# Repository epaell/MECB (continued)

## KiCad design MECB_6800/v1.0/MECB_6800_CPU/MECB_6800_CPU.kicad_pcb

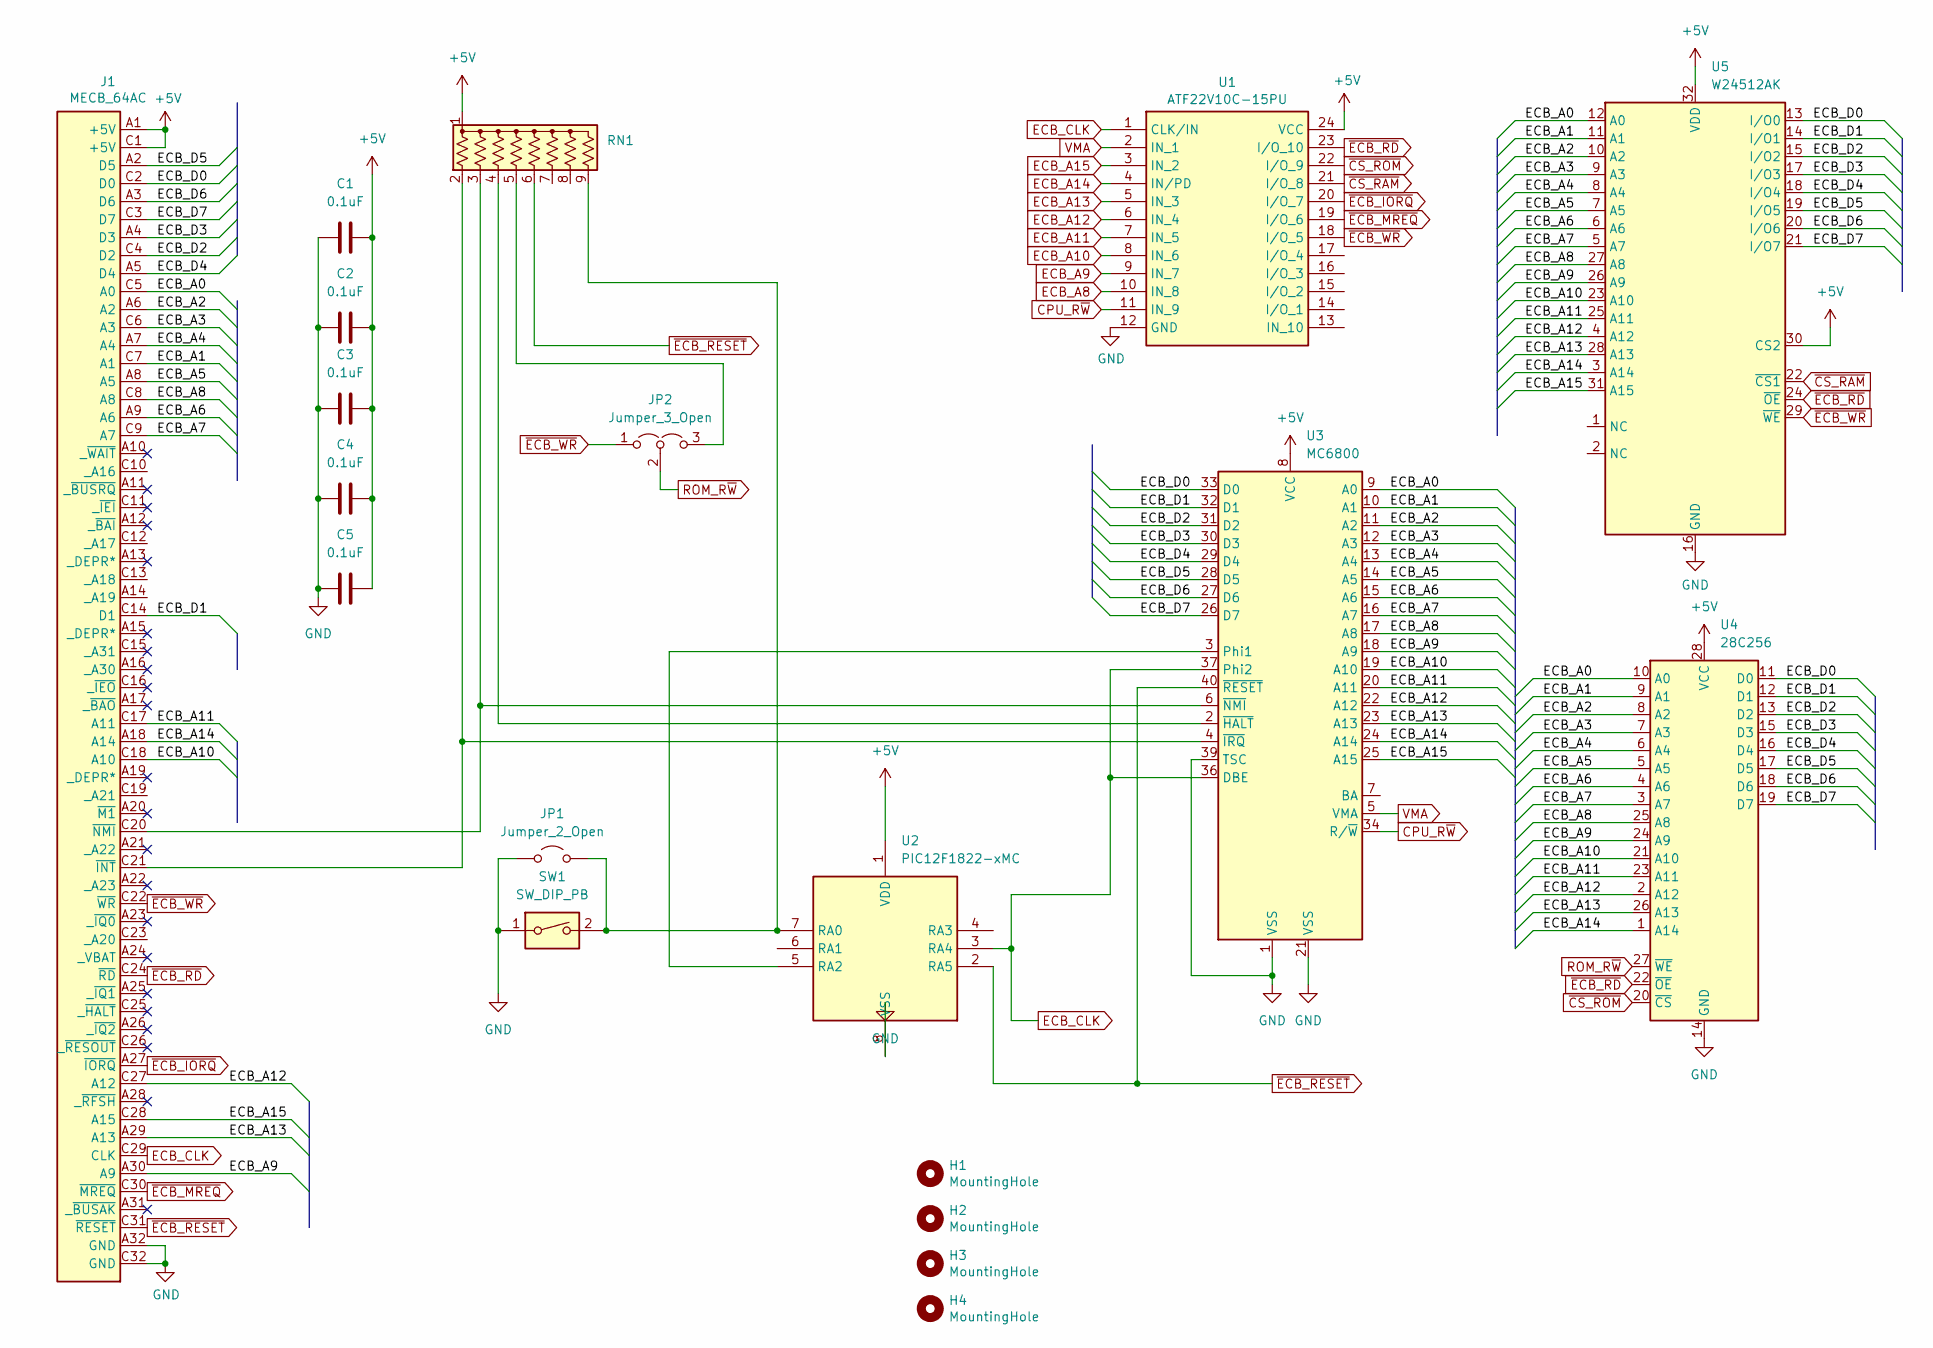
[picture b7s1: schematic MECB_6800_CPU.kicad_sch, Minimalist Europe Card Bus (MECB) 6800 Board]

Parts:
C1, C2, C3, C4, C5: 0.1uF; C_Disc_D5.0mm_W2.5mm_P5.00mm
H1, H2, H3, H4: MountingHole; MountingHole_3.2mm_M3
J1: MECB_64AC; DIN41612_C_2x32_C64AC_Male_Horizontal_THT
JP1: Jumper_2_Open; PinHeader_1x02_P2.54mm_Vertical
JP2: Jumper_3_Open; PinHeader_1x03_P2.54mm_Vertical
RN1: R_Network08_US; R_Array_SIP9
SW1: SW_DIP_PB; SW_Tactile_Straight_KSA0Axx1LFTR
U1: ATF22V10C-15PU; DIP-24_W7.62mm_Socket_LongPads; Mouser Part Number 556-AF22V10C15PU
U2: PIC12F1822-xMC; DIP-8_W7.62mm_Socket_LongPads
U3: MC6800; DIP-40_W15.24mm_Socket_LongPads
U4: 28C256; DIP-28_W15.24mm_Socket_LongPads
U5: W24512AK; DIP-32_W7.62mm

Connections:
+5V: C1.2, C2.2, C3.2, C4.2, C5.2, J1.A1 (+5V), J1.C1 (+5V), RN1.1 (common), U1.24 (VCC), U2.1 (VDD), U3.8 (VCC), U4.28 (VCC), U5.30 (CS2), U5.32 (VDD)
/ECB_A0: J1.C5 (A0), U3.9 (A0), U4.10 (A0), U5.12 (A0)
/ECB_A1: J1.C7 (A1), U3.10 (A1), U4.9 (A1), U5.11 (A1)
/ECB_A2: J1.A6 (A2), U3.11 (A2), U4.8 (A2), U5.10 (A2)
/ECB_A3: J1.C6 (A3), U3.12 (A3), U4.7 (A3), U5.9 (A3)
/ECB_A4: J1.A7 (A4), U3.13 (A4), U4.6 (A4), U5.8 (A4)
/ECB_A5: J1.A8 (A5), U3.14 (A5), U4.5 (A5), U5.7 (A5)
/ECB_A6: J1.A9 (A6), U3.15 (A6), U4.4 (A6), U5.6 (A6)
/ECB_A7: J1.C9 (A7), U3.16 (A7), U4.3 (A7), U5.5 (A7)
/ECB_D0: J1.C2 (D0), U3.33 (D0), U4.11 (D0), U5.13 (I/O0)
/ECB_D1: J1.C14 (D1), U3.32 (D1), U4.12 (D1), U5.14 (I/O1)
/ECB_D2: J1.C4 (D2), U3.31 (D2), U4.13 (D2), U5.15 (I/O2)
/ECB_D3: J1.A4 (D3), U3.30 (D3), U4.15 (D3), U5.17 (I/O3)
/ECB_D4: J1.A5 (D4), U3.29 (D4), U4.16 (D4), U5.18 (I/O4)
/ECB_D5: J1.A2 (D5), U3.28 (D5), U4.17 (D5), U5.19 (I/O5)
/ECB_D6: J1.A3 (D6), U3.27 (D6), U4.18 (D6), U5.20 (I/O6)
/ECB_D7: J1.C3 (D7), U3.26 (D7), U4.19 (D7), U5.21 (I/O7)
CPU_R~W: U1.11 (IN_9), U3.34 (R/~W)
ECB_A8: J1.C8 (A8), U1.10 (IN_8), U3.17 (A8), U4.25 (A8), U5.27 (A8)
ECB_A9: J1.A30 (A9), U1.9 (IN_7), U3.18 (A9), U4.24 (A9), U5.26 (A9)
ECB_A10: J1.C18 (A10), U1.8 (IN_6), U3.19 (A10), U4.21 (A10), U5.23 (A10)
ECB_A11: J1.C17 (A11), U1.7 (IN_5), U3.20 (A11), U4.23 (A11), U5.25 (A11)
ECB_A12: J1.C27 (A12), U1.6 (IN_4), U3.22 (A12), U4.2 (A12), U5.4 (A12)
ECB_A13: J1.A29 (A13), U1.5 (IN_3), U3.23 (A13), U4.26 (A13), U5.28 (A13)
ECB_A14: J1.A18 (A14), U1.4 (IN/PD), U3.24 (A14), U4.1 (A14), U5.3 (A14)
ECB_A15: J1.C28 (A15), U1.3 (IN_2), U3.25 (A15), U5.31 (A15)
ECB_CLK: J1.C29 (CLK), U1.1 (CLK/IN), U2.3 (RA4), U3.36 (DBE), U3.37 (Phi2)
GND: C1.1, C2.1, C3.1, C4.1, C5.1, J1.A32 (GND), J1.C32 (GND), JP1.1 (A), SW1.1, U1.12 (GND), U2.8 (VSS), U3.1 (VSS), U3.21 (VSS), U3.39 (TSC), U4.14 (GND), U5.16 (GND)
unnamed: J1.C21 (~INT), RN1.2 (R1), U3.4 (~IRQ)
unnamed: J1.C20 (~NMI), RN1.3 (R2), U3.6 (~NMI)
unnamed: JP1.2 (B), RN1.9 (R8), SW1.2, U2.7 (RA0)
unnamed: JP2.3 (B), RN1.5 (R4)
unnamed: RN1.4 (R3), U3.2 (~HALT)
unnamed: U2.5 (RA2), U3.3 (Phi1)
ROM_R~W: JP2.2 (C), U4.27 (~WE)
VMA: U1.2 (IN_1), U3.5 (VMA)
~CS_RAM: U1.21 (I/O_8), U5.22 (~CS1)
~CS_ROM: U1.22 (I/O_9), U4.20 (~CS)
~ECB_IORQ: J1.A27 (~IORQ), U1.20 (I/O_7)
~ECB_MREQ: J1.C30 (~MREQ), U1.19 (I/O_6)
~ECB_RD: J1.C24 (~RD), U1.23 (I/O_10), U4.22 (~OE), U5.24 (~OE)
~ECB_RESET: J1.C31 (~RESET), RN1.6 (R5), U2.2 (RA5), U3.40 (~RESET)
~ECB_WR: J1.C22 (~WR), JP2.1 (A), U1.18 (I/O_5), U5.29 (~WE)

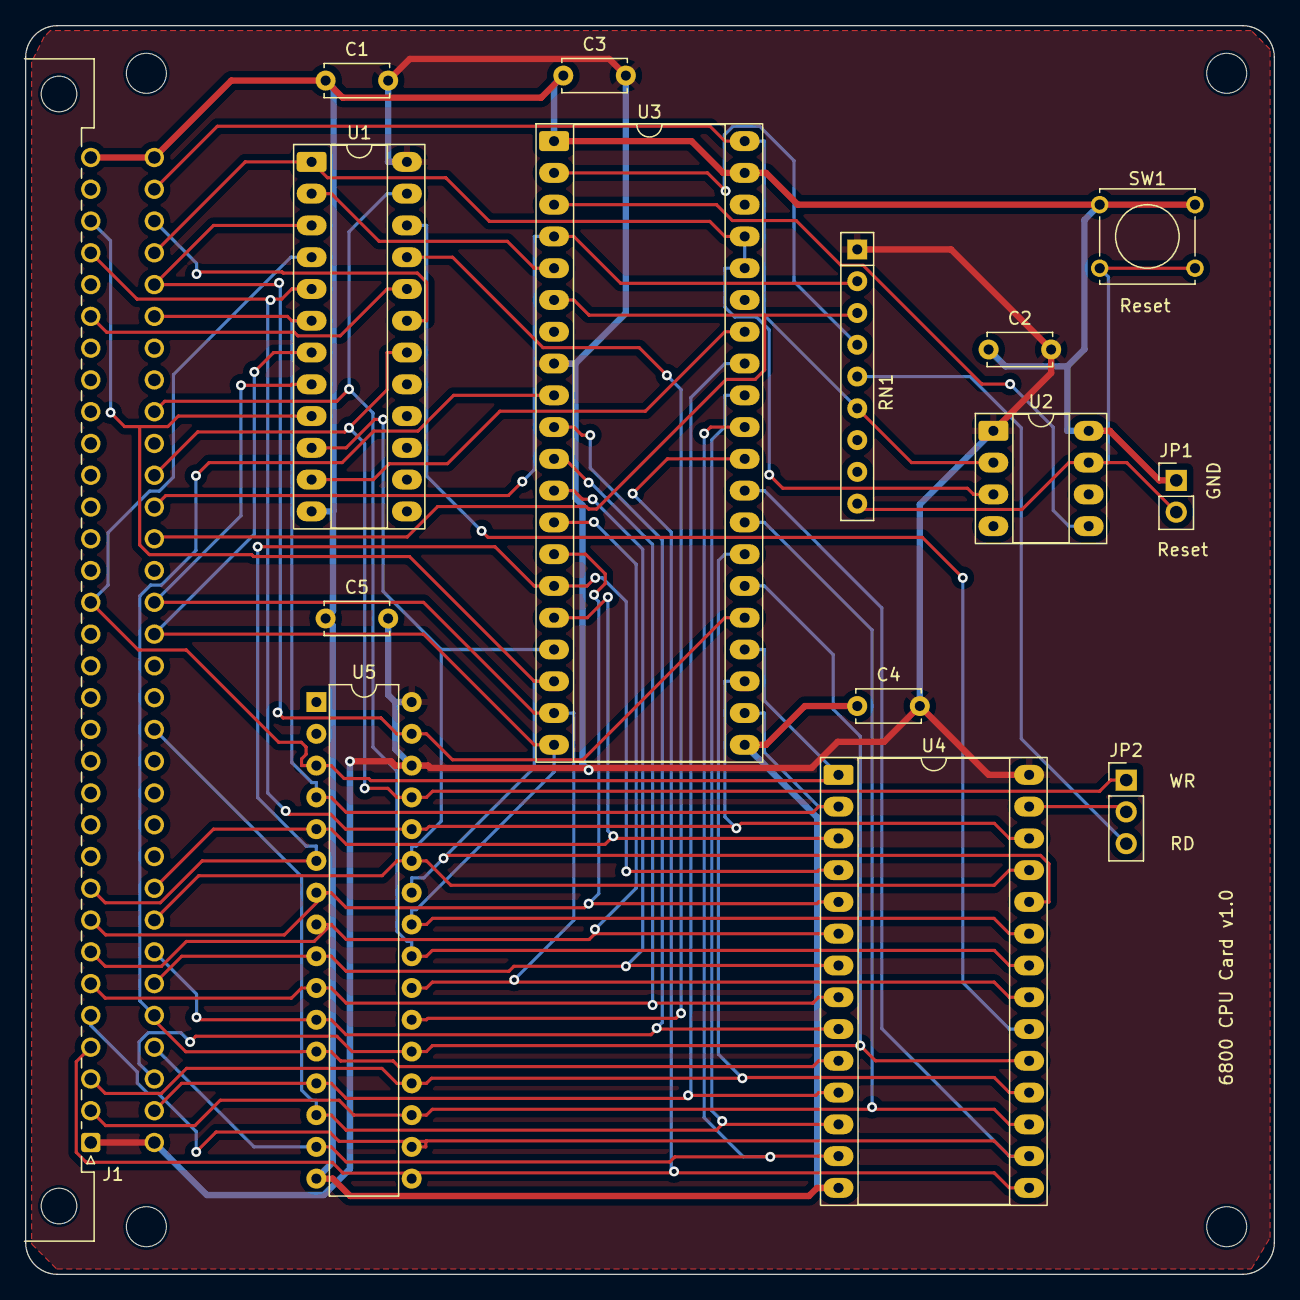
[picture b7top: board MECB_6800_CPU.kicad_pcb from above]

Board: 2 copper layers, 99.8 x 99.8 mm, 19 parts (0 on the bottom side), 43 nets.

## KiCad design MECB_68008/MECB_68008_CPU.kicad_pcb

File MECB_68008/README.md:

# MECB_68008
Development of a MECB 68008 system. Currently this board is under test so use schematics with caution (PCB layout has not been updated with fixes yet). ROM, RAM and IO access have been tested.

TODO:
- test ability to load software via Tutor - OK!
- test board with 9958 VDP card - OK!
- test interrupt functionality - Seems to work with timer.
- test ability to write to FLASH ROM and check write-protect - seems OK.
- test expansion capability - Seems to function OK with ROM expansion card.
- rework the PLD to concentrate addressing in one PLD and remaining GLUE in the other. Currently it is quite messy.
- rework the PCB layout to be incorporate the bodge fixes needed for v0.1.

The GAL directory contains the definition files for the GALs used on the board.

The Tutor directory contains the monitor and enhanced BASIC (modified slightly for use with this system).

The test directory contains a number of very basic test programs to check the ROM, RAM and IO.

The SW directory contains useful 68008-related assembly routines (work in progress). Some of these may ultimately be shifted into ROM.

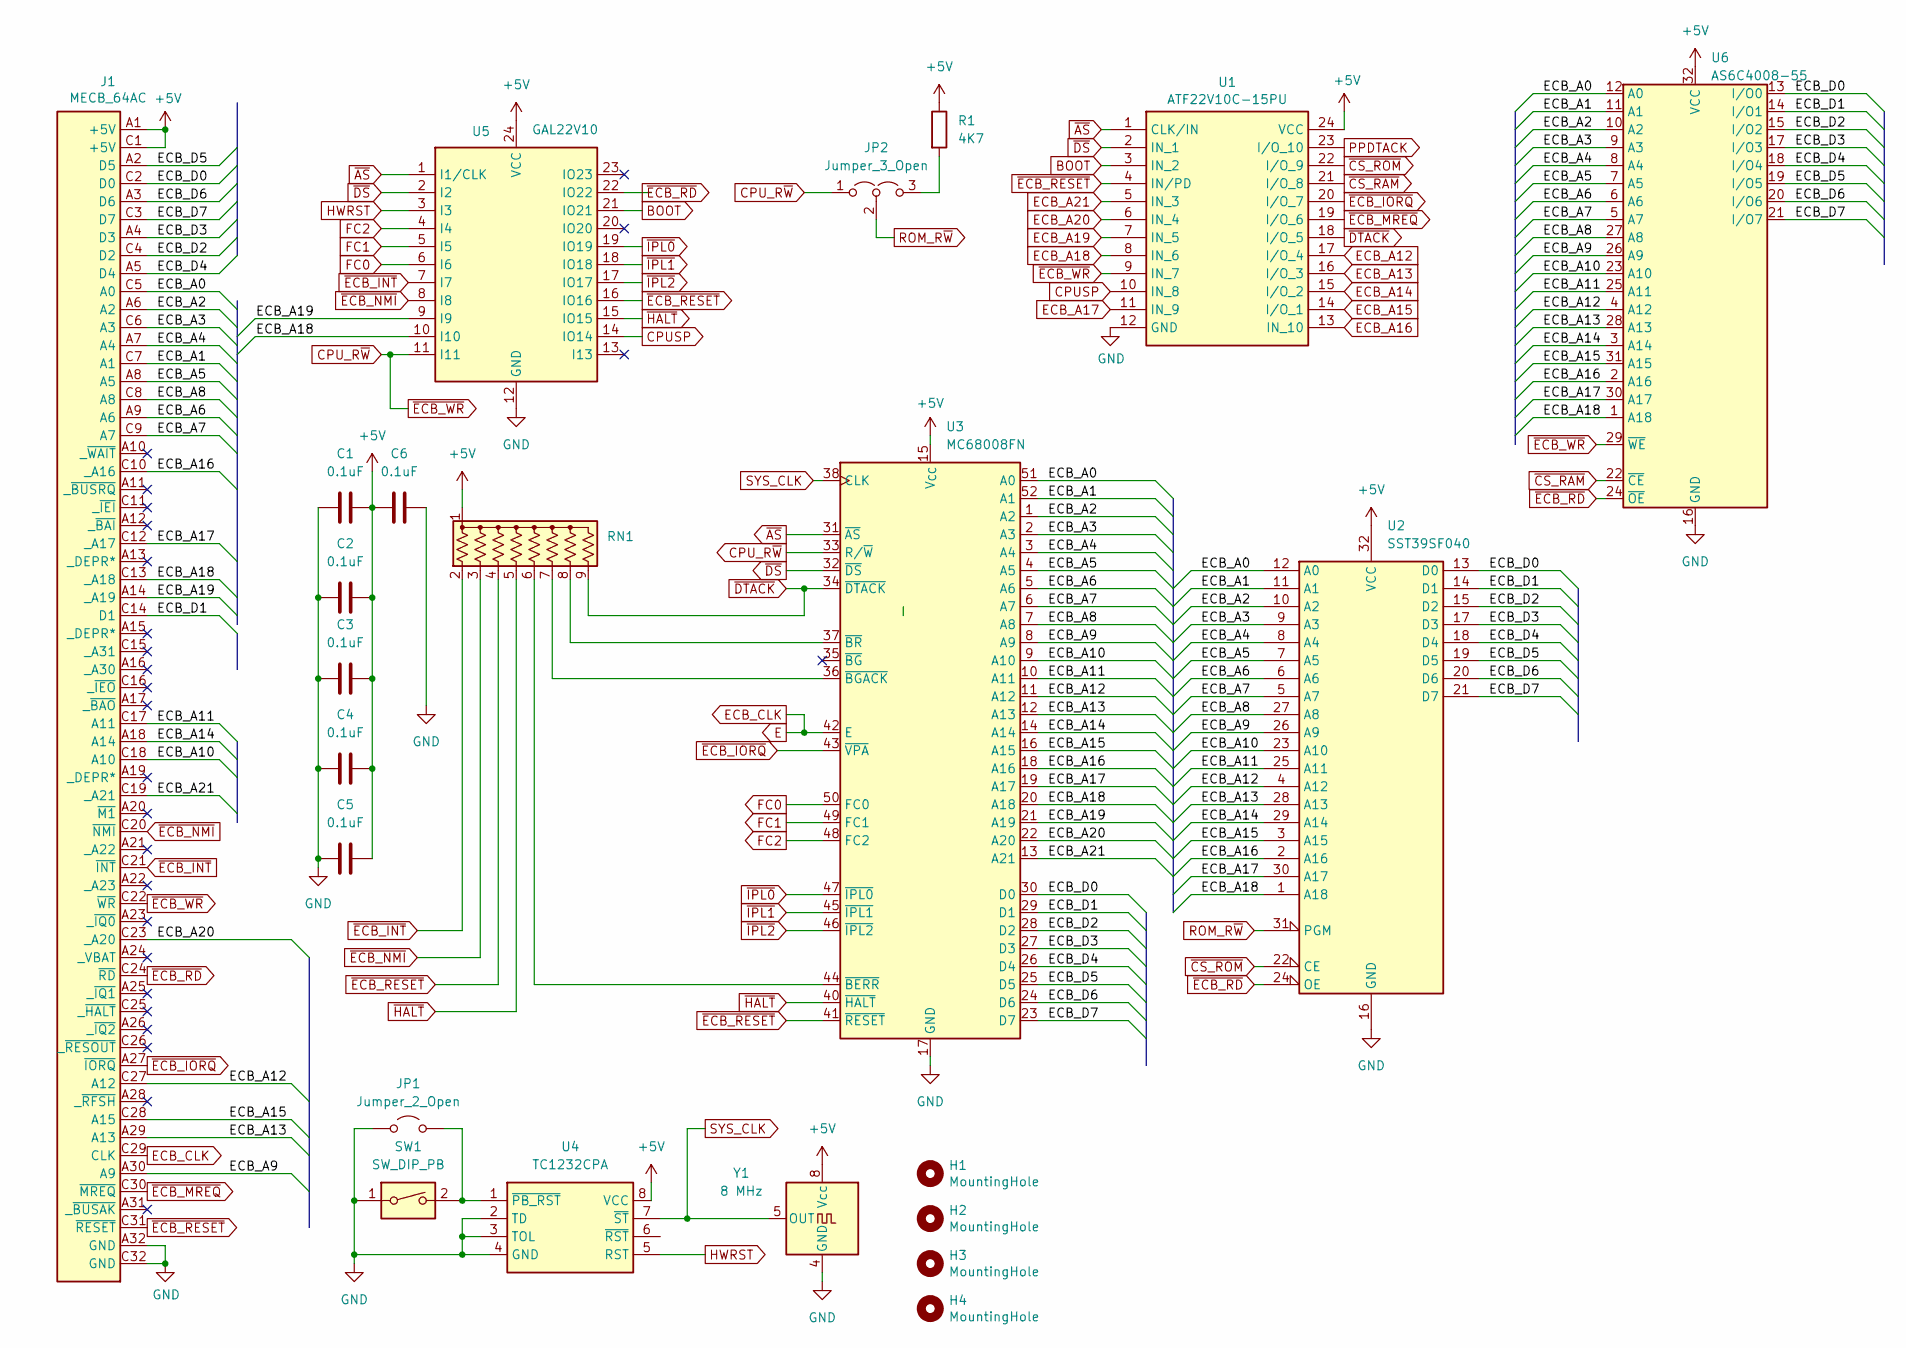
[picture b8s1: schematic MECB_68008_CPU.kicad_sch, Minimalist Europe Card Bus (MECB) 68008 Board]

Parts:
C1, C2, C3, C4, C5, C6: 0.1uF; C_Disc_D5.0mm_W2.5mm_P5.00mm
H1, H2, H3, H4: MountingHole; MountingHole_3.2mm_M3
J1: MECB_64AC; DIN41612_C_2x32_C64AC_Male_Horizontal_THT
JP1: Jumper_2_Open; PinHeader_1x02_P2.54mm_Vertical
JP2: Jumper_3_Open; PinHeader_1x03_P2.54mm_Vertical
R1: 4K7; R_Axial_DIN0309_L9.0mm_D3.2mm_P12.70mm_Horizontal
RN1: R_Network08_US; R_Array_SIP9
SW1: SW_DIP_PB; SW_Tactile_Straight_KSA0Axx1LFTR
U1: ATF22V10C-15PU; DIP-24_W7.62mm_Socket_LongPads_ZIF_Friendly; Mouser Part Number 556-AF22V10C15PU
U2: SST39SF040; DIP-32_W15.24mm_Socket_LongPads
U3: MC68008FN; PLCC-52_THT-Socket
U4: TC1232CPA; DIP-8_W7.62mm_Socket_LongPads
U5: GAL22V10; DIP-24_W7.62mm_Socket_LongPads
U6: AS6C4008-55; DIP-32_W15.24mm_Socket_LongPads
Y1: 8 MHz; DIP-4-8_W7.62mm_Socket_LongPads

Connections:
+5V: C1.2, C2.2, C3.2, C4.2, C5.2, C6.1, J1.A1 (+5V), J1.C1 (+5V), R1.1, RN1.1 (common), U1.24 (VCC), U2.32 (VCC), U3.15 (V_{CC}), U4.8 (VCC), U5.24 (VCC), U6.32 (VCC), Y1.8 (Vcc)
/ECB_A0: J1.C5 (A0), U2.12 (A0), U3.51 (A0), U6.12 (A0)
/ECB_A1: J1.C7 (A1), U2.11 (A1), U3.52 (A1), U6.11 (A1)
/ECB_A2: J1.A6 (A2), U2.10 (A2), U3.1 (A2), U6.10 (A2)
/ECB_A3: J1.C6 (A3), U2.9 (A3), U3.2 (A3), U6.9 (A3)
/ECB_A4: J1.A7 (A4), U2.8 (A4), U3.3 (A4), U6.8 (A4)
/ECB_A5: J1.A8 (A5), U2.7 (A5), U3.4 (A5), U6.7 (A5)
/ECB_A6: J1.A9 (A6), U2.6 (A6), U3.5 (A6), U6.6 (A6)
/ECB_A7: J1.C9 (A7), U2.5 (A7), U3.6 (A7), U6.5 (A7)
/ECB_A8: J1.C8 (A8), U2.27 (A8), U3.7 (A8), U6.27 (A8)
/ECB_A9: J1.A30 (A9), U2.26 (A9), U3.8 (A9), U6.26 (A9)
/ECB_A10: J1.C18 (A10), U2.23 (A10), U3.9 (A10), U6.23 (A10)
/ECB_A11: J1.C17 (A11), U2.25 (A11), U3.10 (A11), U6.25 (A11)
/ECB_D0: J1.C2 (D0), U2.13 (D0), U3.30 (D0), U6.13 (I/O0)
/ECB_D1: J1.C14 (D1), U2.14 (D1), U3.29 (D1), U6.14 (I/O1)
/ECB_D2: J1.C4 (D2), U2.15 (D2), U3.28 (D2), U6.15 (I/O2)
/ECB_D3: J1.A4 (D3), U2.17 (D3), U3.27 (D3), U6.17 (I/O3)
/ECB_D4: J1.A5 (D4), U2.18 (D4), U3.26 (D4), U6.18 (I/O4)
/ECB_D5: J1.A2 (D5), U2.19 (D5), U3.25 (D5), U6.19 (I/O5)
/ECB_D6: J1.A3 (D6), U2.20 (D6), U3.24 (D6), U6.20 (I/O6)
/ECB_D7: J1.C3 (D7), U2.21 (D7), U3.23 (D7), U6.21 (I/O7)
BOOT: U1.3 (IN_2), U5.21 (IO21)
CPUSP: U1.10 (IN_8), U5.14 (IO14)
CPU_R~W: J1.C22 (~WR), JP2.1 (A), U1.9 (IN_7), U3.33 (R/~W), U5.11 (I11), U6.29 (~WE)
E: J1.C29 (CLK), U3.42 (E)
ECB_A12: J1.C27 (A12), U1.17 (I/O_4), U2.4 (A12), U3.11 (A12), U6.4 (A12)
ECB_A13: J1.A29 (A13), U1.16 (I/O_3), U2.28 (A13), U3.12 (A13), U6.28 (A13)
ECB_A14: J1.A18 (A14), U1.15 (I/O_2), U2.29 (A14), U3.14 (A14), U6.3 (A14)
ECB_A15: J1.C28 (A15), U1.14 (I/O_1), U2.3 (A15), U3.16 (A15), U6.31 (A15)
ECB_A16: J1.C10 (_A16), U1.13 (IN_10), U2.2 (A16), U3.18 (A16), U6.2 (A16)
ECB_A17: J1.C12 (_A17), U1.11 (IN_9), U2.30 (A17), U3.19 (A17), U6.30 (A17)
ECB_A18: J1.C13 (_A18), U1.8 (IN_6), U2.1 (A18), U3.20 (A18), U5.10 (I10), U6.1 (A18)
ECB_A19: J1.A14 (_A19), U1.7 (IN_5), U3.21 (A19), U5.9 (I9)
ECB_A20: J1.C23 (_A20), U1.6 (IN_4), U3.22 (A20)
ECB_A21: J1.C19 (_A21), U1.5 (IN_3), U3.13 (A21)
FC0: U3.50 (FC0), U5.6 (I6)
FC1: U3.49 (FC1), U5.5 (I5)
FC2: U3.48 (FC2), U5.4 (I4)
GND: C1.1, C2.1, C3.1, C4.1, C5.1, C6.2, J1.A32 (GND), J1.C32 (GND), JP1.1 (A), SW1.1, U1.12 (GND), U2.16 (GND), U3.17 (GND), U3.39 (GND), U4.2 (TD), U4.3 (TOL), U4.4 (GND), U5.12 (GND), U6.16 (GND), Y1.4 (GND)
HWRST: U4.5 (RST), U5.3 (I3)
unnamed: JP1.2 (B), SW1.2, U4.1 (~PB_RST)
unnamed: JP2.3 (B), R1.2
unnamed: RN1.6 (R5), U3.44 (~BERR)
unnamed: RN1.7 (R6), U3.36 (~BGACK)
unnamed: RN1.8 (R7), U3.37 (~BR)
PPDTACK: U1.23 (I/O_10)
ROM_R~W: JP2.2 (C), U2.31 (PGM)
SYS_CLK: U3.38 (CLK), U4.7 (~ST), Y1.5 (OUT)
~AS: U1.1 (CLK/IN), U3.31 (~AS), U5.1 (I1/CLK)
~CS_RAM: U1.21 (I/O_8), U6.22 (~CE)
~CS_ROM: U1.22 (I/O_9), U2.22 (CE)
~DS: U1.2 (IN_1), U3.32 (~DS), U5.2 (I2)
~DTACK: RN1.9 (R8), U1.18 (I/O_5), U3.34 (~DTACK)
~ECB_INT: J1.C21 (~INT), RN1.2 (R1), U5.7 (I7)
~ECB_IORQ: J1.A27 (~IORQ), U1.20 (I/O_7), U3.43 (~VPA)
~ECB_MREQ: J1.C30 (~MREQ), U1.19 (I/O_6)
~ECB_NMI: J1.C20 (~NMI), RN1.3 (R2), U5.8 (I8)
~ECB_RD: J1.C24 (~RD), U2.24 (OE), U5.22 (IO22), U6.24 (~OE)
~ECB_RESET: J1.C31 (~RESET), RN1.4 (R3), U1.4 (IN/PD), U3.41 (~RESET), U5.16 (IO16)
~HALT: RN1.5 (R4), U3.40 (~HALT), U5.15 (IO15)
~IPL0: U3.47 (~IPL0), U5.19 (IO19)
~IPL1: U3.45 (~IPL1), U5.18 (IO18)
~IPL2: U3.46 (~IPL2), U5.17 (IO17)

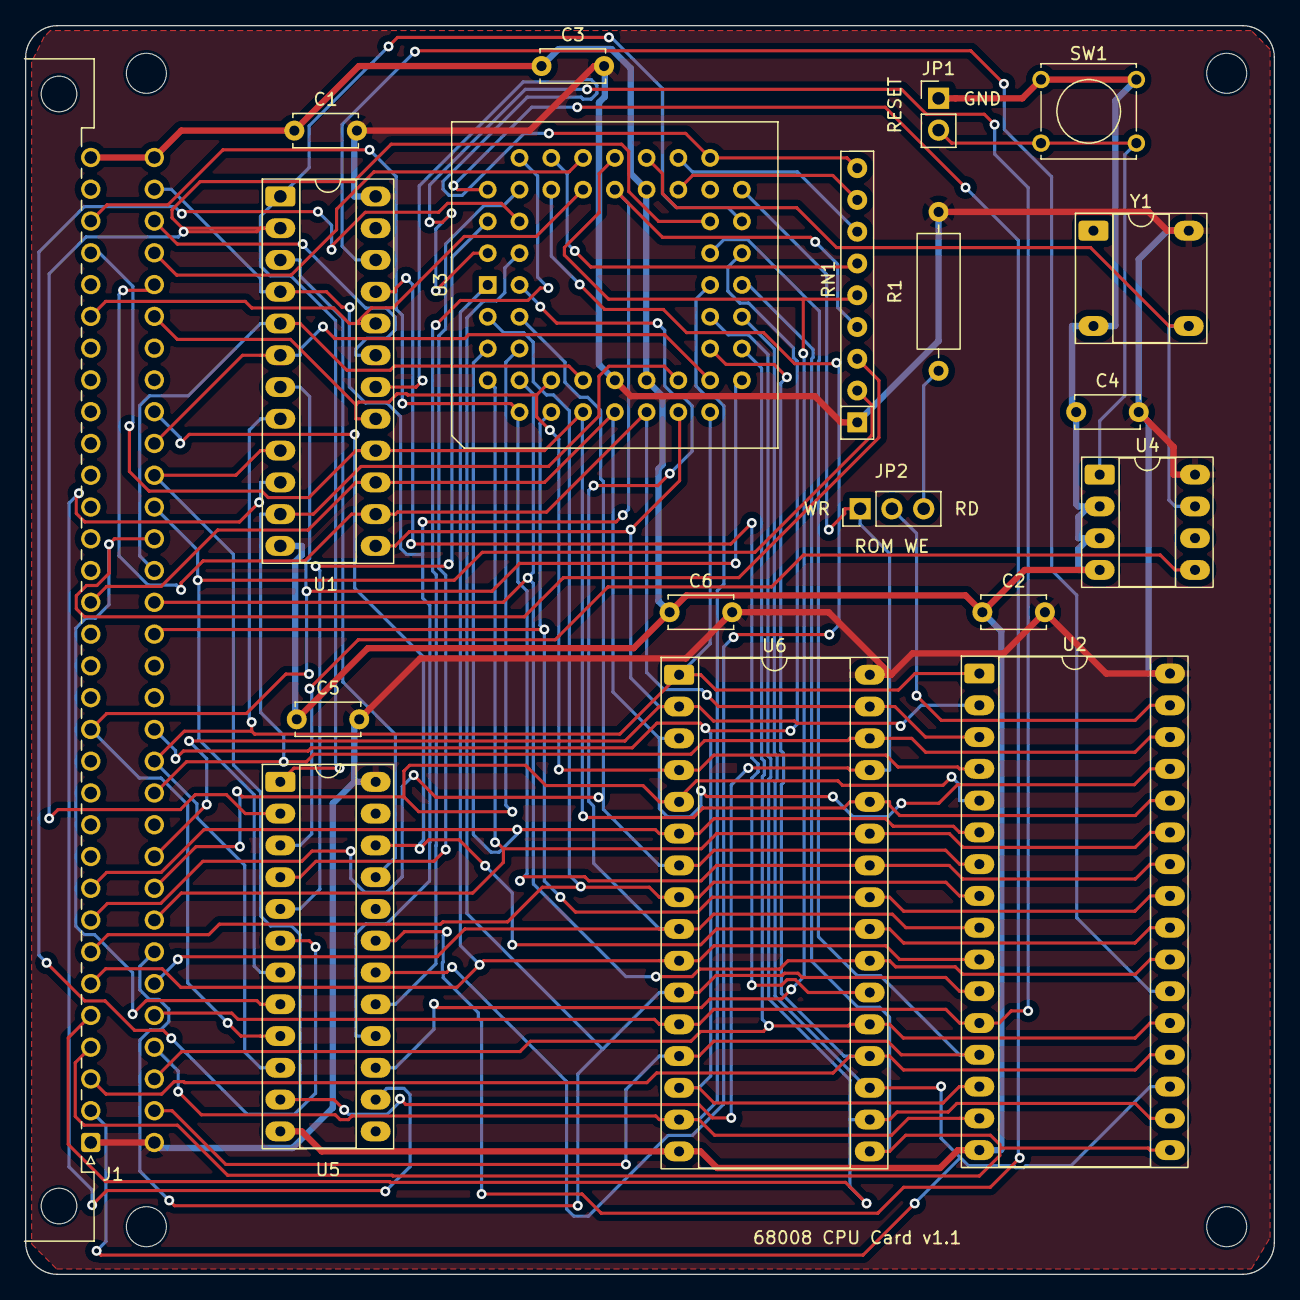
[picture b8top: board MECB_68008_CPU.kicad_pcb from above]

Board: 2 copper layers, 99.8 x 99.8 mm, 23 parts (0 on the bottom side), 62 nets.

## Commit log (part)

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2024-07-02 Added FLASH test code
2024-07-02 Added more details to README
2024-07-02 Added combined code
2024-07-02 Fix structure
2024-07-02 Reorganize things
2024-07-02 Added README
2024-07-03 Operations now check FLASH status
2024-07-04 Added the FLASHable binary
2024-07-04 Initial version
2024-07-04 Modified to work with MECB 6502
2024-07-04 Modifications for MECB
2024-07-04 Modified README to cite original source
2024-07-04 Base version
2024-07-04 Modified for MECB
2024-07-04 More citations
2024-07-04 Initial version of osi basic
2024-07-05 Added help for R command
2024-07-09 Added MAME emulation of MECB
2024-07-10 Added hypothetical MECB 68008
2024-07-10 Added original Tutor code
2024-07-10 Modified to work with MECB
2024-07-10 Added mecb68008t with the tutor monitor
2024-07-10 Added the tutor ROM
2024-07-10 Added EHBASIC
2024-07-10 EHBASIC modified for MECB
2024-07-10 Fixed readme
2024-07-10 Added BASIC to MECB MAME
2024-07-11 Fiddled vector space a bit
2024-07-11 Trap 14 now works in tutor
2024-07-11 Added a combined version of 68008 ROM containing Tutor and Enhanced BASIC
2024-07-12 Initial version of MECB Z80
2024-07-12 Modified Z80 to work with MAME
2024-07-12 Added a Z80 machine
2024-07-12 More updates
2024-07-13 Minor improvements
2024-07-20 Added timer example for 6502
2024-07-22 Added VDP support
2024-07-23 Fixed typo
2024-07-23 Initial version of compilable code
2024-07-24 Added a version of ASSIST09 with some disk subtroutines
2024-07-24 Changed IO location to suite FLEX
2024-07-24 FLEX disk images and tools
2024-07-24 Added microSDcard shield project
2024-07-24 Added arduino software
2024-07-24 Clean up
2024-07-25 Original version
2024-07-25 Modified for MECB version
2024-07-25 Added timer functionality and moved 68008 ACIA to make it consistent with other MECB IO configurations
2024-07-25 Initial plasma code
2024-07-25 Updated for MECB
2024-08-22 Cleaned up handling of checksum updates
2025-09-09 Some tests for MECB OLED display
2025-09-23 Added circle function
2025-10-27 Added initial MECB 68008 board files
2025-10-27 68008 tester
2025-10-27 Gerbers for initial test board - note that MECB_RD and MECB_WR erroneously have inverted active state
2025-10-31 Updated some software
2025-10-31 Reshuffling
2025-10-31 move ZBUG
2025-10-31 Move BASIC
2025-10-31 Remove old build
2025-10-31 Updated Readme file
2025-10-31 Updated schematic
2025-11-02 Minor fix to u5.pld to fix interrupts after breaking them
2025-11-03 Version 0.1 of the schematic complete
2025-11-03 Updated build
2025-11-03 Updated flash routines
2025-11-04 Updated FLASH ROM routines
2025-11-07 Initial routines for working with SD card
2025-11-10 Added OLED routines
2025-11-10 Added extra test programs
2025-11-14 Added math library
2025-11-14 Added library compilation for rom
2025-11-14 Added library version that can be added to main on-board ROM
2025-11-14 Removed some old code
2025-11-14 combine expansion and non-expansion rom compilation
2025-11-21 Reorganised for library flashing and added circle function
2025-11-21 spring clean
2025-11-21 Script to compile and generate library related files
2025-11-22 v1.1 board finalised
2025-12-01 Updated some code
2025-12-01 Updated Gerbers
2025-12-02 Minor fix
2026-01-17 v1 of 6800 board
2026-01-18 Moved files
2026-01-18 v1 files
2026-01-18 Modified u1 to extend memory
2026-01-29 Basic monitor
2026-01-29 Added readme files
2026-01-29 Added final pld definitions
2026-01-29 Added Kicad files
2026-01-29 Removed old files
2026-01-30 Updated monitor
2026-01-31 Cleaned up a few things
2026-02-07 v1.1 - fix for missing ECB_CLK signal
2026-02-14 Updated memory test
2026-03-04 Partially complete v1.0 design
2026-03-06 More tests for Z80 card
2026-03-07 Minor fixes for v1.0
2026-03-11 v1.1 8088 board
2026-03-20 Minor changes for v1.0 IDE card
2026-03-24 v1.0 Z80 Board tested
2026-03-25 v0.1 of IO board added
2026-03-25 Added note to remove pin 20 of 44 pin header
2026-03-26 V1.0 board should fix the RTC issue
2026-03-26 Minor improvements for V1.0 board
2026-04-06 Finalised GAL Code for v1.0 IDE
2026-04-06 Sample images
2026-04-06 Added photo
2026-04-07 Added label to indicate pin on J2 needs to be removed
2026-04-07 Add note about removing pin 20 on both IDE headers
2026-04-07 Updated image with pin 20 removed
2026-05-15 Version 1.0 of PS2 interface is operational
2026-05-16 Added test programs for MECB SID card
2026-05-16 Uploaded v0.1 of SID card
2026-05-25 Test reading raw sectors from IDE using 68008
2026-06-06 Added SID tunes for testing MECB-SID card
2026-06-06 Shifted second SID to
2026-06-07 Updated readme - new update needed to work with clocks higher than 1 MHz
2026-06-09 Added Fujinet board
